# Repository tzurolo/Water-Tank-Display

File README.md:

# Water-Tank-Display

Display module for the Water Tank Monitor.

It will be located in the pump house.

From there it will also monitor mains status and the operation of the pump.

It is based on the Adafruit Feather FONA 32u4 cellular module and an Adafruit TFT display.

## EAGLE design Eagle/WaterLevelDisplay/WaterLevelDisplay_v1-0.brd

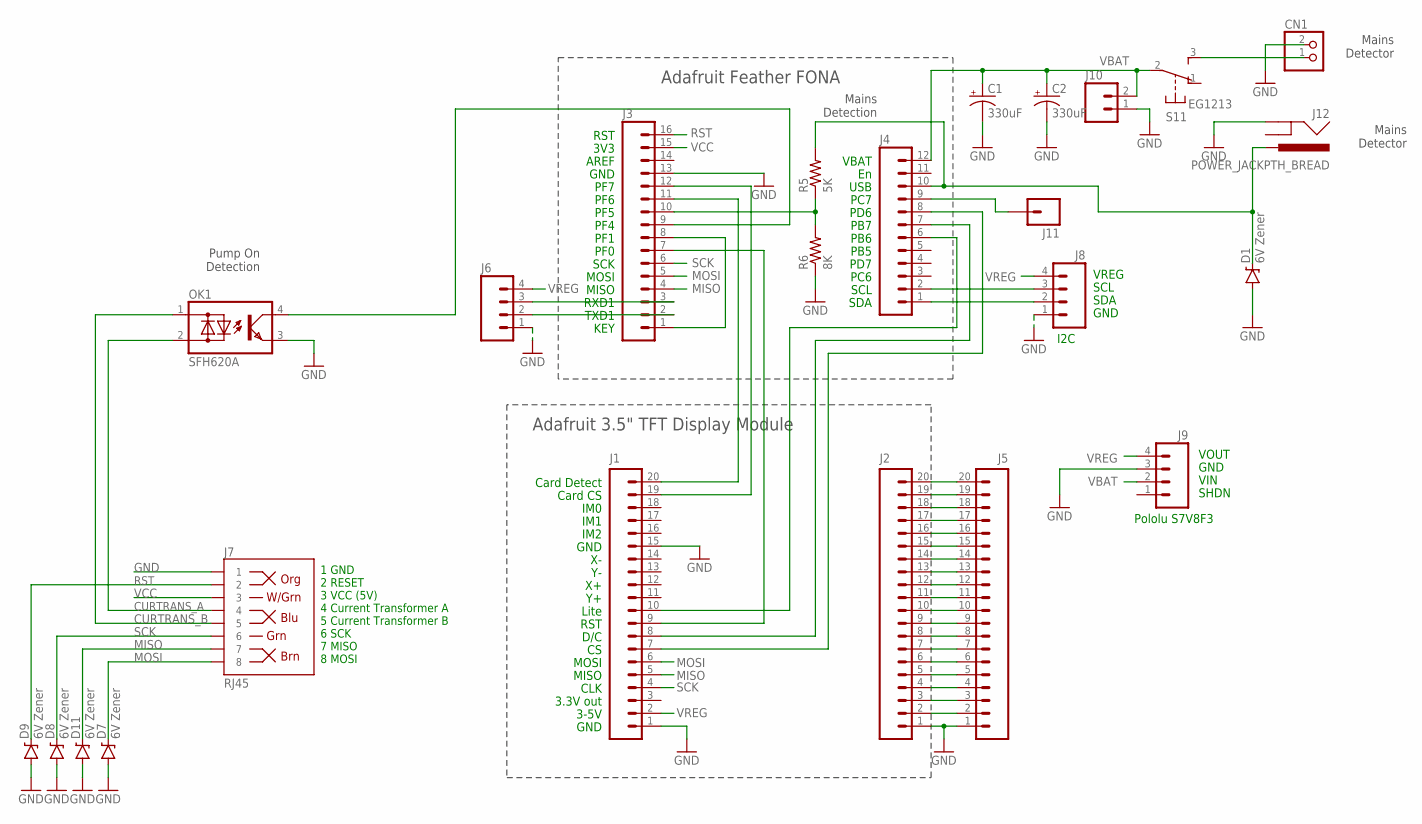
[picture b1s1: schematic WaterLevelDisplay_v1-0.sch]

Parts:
C1, C2: 330uF; CPOL-RADIAL-100UF-25V
CN1: JST_2PIN-SMT-RA; JST-PH-2-SMT-RA
D1, D7, D8, D9, D11: 6V Zener; DIODE-ZENER
J1, J2, J5: M20NOSILK; 1X20_NOSILK
J3: M161X16_NO_SILK; 1X16_NO_SILK
J4: M12NO_SILK; 1X12_NO_SILK
J6, J8, J9: M04PTH; 1X04
J7: RJ45; RJ45-8
J10: M02PTH; 1X02
J11: M01PTH; 1X01
J12: POWER_JACKPTH_BREAD; POWER_JACK_PTH_BREAD
OK1: SFH620A; DIL04
R5: 5K; 0204/5
R6: 8K; 0204/5
S1: EG1213

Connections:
CURTRANS_A: J7.4, OK1.2 (AC2)
CURTRANS_B: J7.5, OK1.1 (AC1)
GND: C1.2 (-), C2.2 (-), CN1.2 (1), D1.P$2 (A), D7.P$2 (A), D8.P$2 (A), D9.P$2 (A), D11.P$2 (A), J1.1, J1.15, J2.1, J3.13, J5.1, J6.1, J7.1, J8.1, J9.3, J10.1, J12.GND, OK1.3 (E), R6.1
MISO: D11.P$1 (C), J1.5, J3.4, J7.7
MOSI: D7.P$1 (C), J1.6, J3.5, J7.8
unnamed: CN1.1 (2), S1.3 (S)
unnamed: J2.2, J5.2
unnamed: J2.3, J5.3
unnamed: J2.4, J5.4
unnamed: J2.5, J5.5
unnamed: J3.3, J6.3
unnamed: J2.6, J5.6
unnamed: J2.7, J5.7
unnamed: J4.9, J11.1
unnamed: J2.8, J5.8
unnamed: J2.9, J5.9
unnamed: J2.10, J5.10
unnamed: J2.11, J5.11
unnamed: J2.12, J5.12
unnamed: J3.1, J3.8
unnamed: J2.13, J5.13
unnamed: D1.P$1 (C), J4.10, J12.PWR, R5.2
unnamed: J3.10, R5.1, R6.2
unnamed: J2.14, J5.14
unnamed: J2.15, J5.15
unnamed: J2.16, J5.16
unnamed: J2.17, J5.17
unnamed: J2.18, J5.18
unnamed: J2.19, J5.19
unnamed: J2.20, J5.20
unnamed: J3.2, J6.2
unnamed: J1.8, J4.7
unnamed: J1.19, J3.12
unnamed: J1.20, J3.11
unnamed: J1.10, J4.6
unnamed: J3.9, OK1.4 (C)
unnamed: J1.7, J4.8
unnamed: J1.9, J3.7
unnamed: J4.1, J8.2
unnamed: J4.2, J8.3
RST: D9.P$1 (C), J3.16, J7.2
SCK: D8.P$1 (C), J1.4, J3.6, J7.6
VBAT: C1.1 (+), C2.1 (+), J4.12, J9.2, J10.2, S1.2
VCC: J3.15, J7.3
VREG: J1.2, J6.4, J8.4, J9.4

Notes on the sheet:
Mains Detection
1 GND 2 RESET 3 VCC (5V) 4 Current Transformer A 5 Current Transformer B 6 SCK 7 MISO 8 MOSI
GND
3.3V out
CLK
MISO
MOSI
D/C
RST
Lite
IM2
IM1
IM0
Card CS
Card Detect
3-5V
3V3
AREF
PF7
PF6
PF5
PF1
PF0
SCK
PF4
TXD1
KEY
RXD1
VBAT
USB
PC7
PD6
PB7
PB6
PB5
PD7
PC6
SCL
SDA
Adafruit Feather FONA

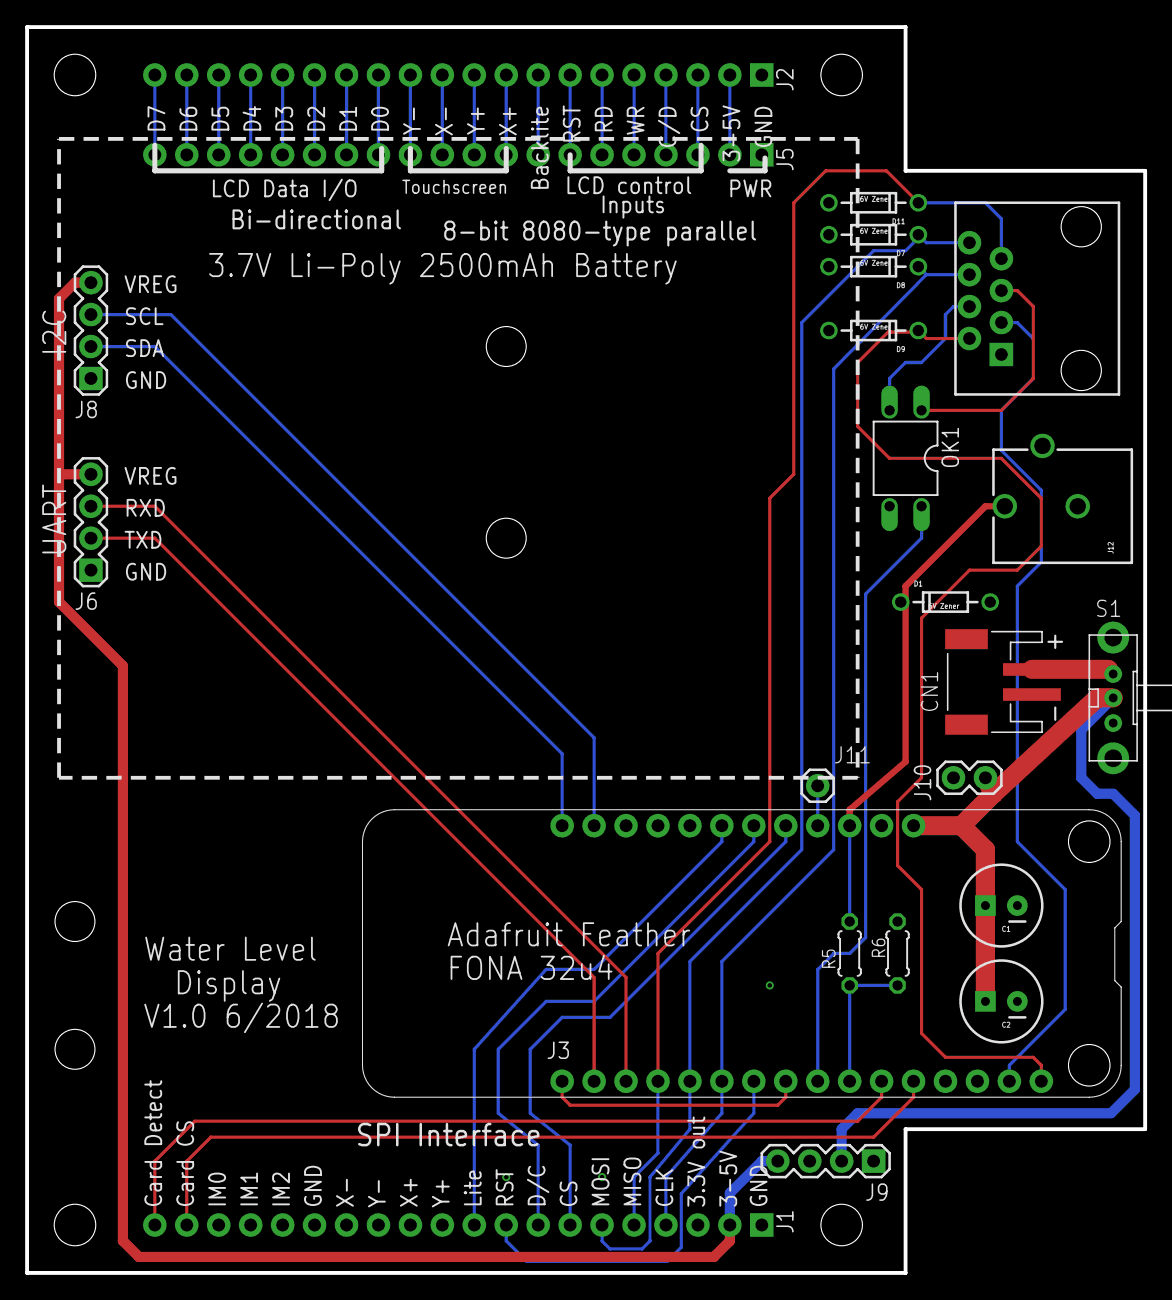
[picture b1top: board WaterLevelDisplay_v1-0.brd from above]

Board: 2 copper layers, 88.9 x 99.1 mm, 30 parts (0 on the bottom side), 45 nets.

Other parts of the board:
U$1, U$2, U$3, U$4, U$5, U$6: STAND-OFF

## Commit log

2018-05-20 wait for cell disabled before adjusting time
2018-05-27 first TFT operational
2018-05-29 initial board layout
    captured footprint of feather fona and TFT board
2018-05-31 first round of layout
2018-05-31 changes to suit PC board layout
2018-06-02 candidate for final
2018-06-06 TFT task
2018-06-07 rectangle drawing working
2018-06-08 timeouts and log delay
2018-06-11 initial text support
2018-06-15 added ADC manager and temperature sensor
2018-06-16 utc offset, display updates
2018-06-16 display updates, fixed scanInteger neg bug
2018-06-17 glyph padding
2018-06-21 CSTT username & password, day of week names
2018-06-23 padded time display
2018-07-04 increased ipserver name size to 60
2018-08-02 command for log delay, change default ip server

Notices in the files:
parts and their libraries:
SparkFun-DiscreteSemi: Licensing: Creative Commons ShareAlike 4.0 International - https://creativecommons.org/licenses/by-sa/4.0
